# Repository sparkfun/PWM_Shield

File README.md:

**NOTE:** *This product has been retired from our catalog. If you are looking for more up-to-date info, please check out some of these resources to see how other users are still hacking and improving on this product.*
* *[SparkFun Forum](https://forum.sparkfun.com/)*
* *[Comments Here on GitHub](https://github.com/sparkfun/PWM_Shield/issues)*
* *[IRC Channel](https://www.sparkfun.com/news/263)*

SparkFun PWM Shield
========================================

[*SparkFun PWM Shield (DEV-10615)*](https://www.sparkfun.com/products/10615)

This is the Arduino shield version of our TLC5940 Breakout. 
The SparkFun PWM Shield will allow you to generate up to 16 PWM signals from your Arduino by utilizing the power of the TLC5940 IC. 

Repository Contents
-------------------

* **/Hardware** - Eagle design files (.brd, .sch)
* **/Libraries** - Libraries for use with the TLC5940
* **/Production** - Production panel files (.brd)

Documentation
--------------
* **[Library](https://github.com/sparkfun/SparkFun_TLC5940_Arduino_Library)** - Arduino Library for the TLC5940. 
* **[SparkFun Fritzing repo](https://github.com/sparkfun/Fritzing_Parts)** - Fritzing diagrams for SparkFun products.
* **[SparkFun 3D Model repo](https://github.com/sparkfun/3D_Models)** - 3D models of SparkFun products. 

License Information
-------------------
This product is _**open source**_! 

The **hardware** is released under [Creative Commons ShareAlike 4.0 International](https://creativecommons.org/licenses/by-sa/4.0/).

Please use, reuse, and modify these files as you see fit. Please maintain attribution to SparkFun Electronics and release anything derivative under the same license.

Distributed as-is; no warranty is given.

- Your friends at SparkFun.

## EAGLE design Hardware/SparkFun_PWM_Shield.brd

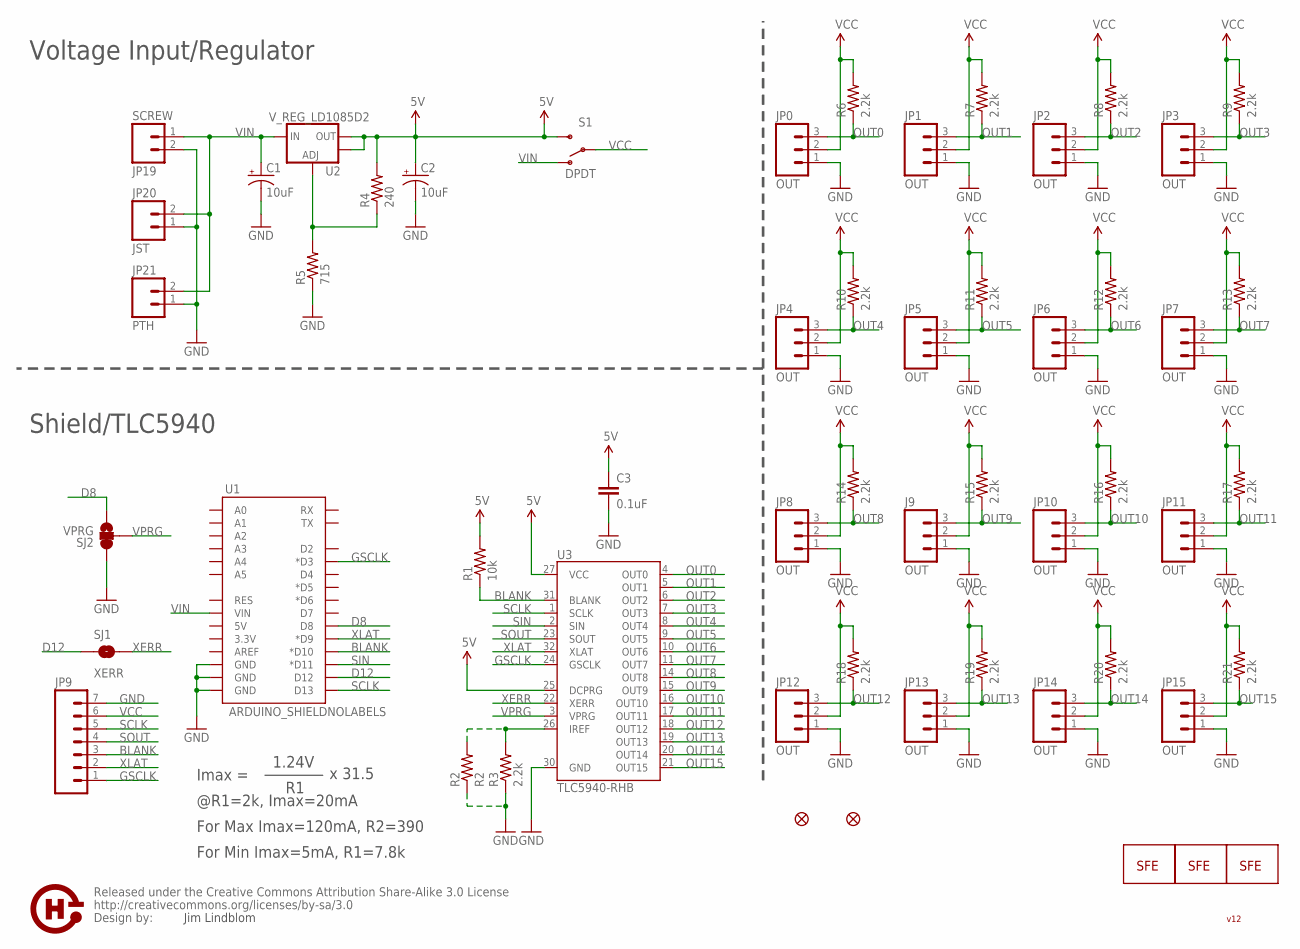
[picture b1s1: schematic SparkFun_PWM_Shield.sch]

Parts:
C1: 10uF; EIA3528
C2: 10uF; EIA3216
C3: 0.1uF; 0402-CAP
J9: OUT; 1X03
JP0, JP1, JP2, JP3, JP4, JP5, JP6, JP7, JP8, JP10, JP11, JP12, JP13, JP14, JP15: OUT; 1X03
JP9: M07; 1X07
JP16: LOGO-SFENEW; SFE-NEW-WEBLOGO
JP17: LOGO-SFESK; SFE-LOGO-FLAME
JP18: LOGO-SFENW2; SFE-NEW-WEB
JP19: SCREW; SCREWTERMINAL-3.5MM-2-NS
JP20: JST; JST-2-PTH
JP21: PTH; 1X02
JP22, JP23: FIDUCIAL1X2; FIDUCIAL-1X2
R1: 10k; 0402-RES
R2: R2; AXIAL-0.3
R3, R6, R7, R8, R9, R10, R11, R12, R13, R14, R15, R16, R17, R18, R19, R20, R21: 2.2k; 0402-RES
R4: 240; 0402-RES
R5: 715; 0402-RES
S1: DPDT; AYZ0202
SJ1: XERR; SJ_2S-NO
SJ2: VPRG; SJ_3
U1: ARDUINO_SHIELDNOLABELS; DUEMILANOVE_SHIELD_NOLABELS
U2: V_REG_LD1085D2; D2PACK/A
U3: TLC5940-RHB; QFN-32
U$1: OSHW-LOGOORB; OSHW-LOGO-GO
U$2: CREATIVE_COMMONS

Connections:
5V: C2.A (+), C3.1, R1.2, R4.2, S1.3 (S), U2.2 (OUT), U2.TAB (OUT), U3.25 (DCPRG), U3.27 (VCC)
BLANK: JP9.3, R1.1, U1.D10 (*D10), U3.31 (BLANK)
D8: SJ2.3, U1.D8
D12: SJ1.1, U1.D12
GND: C1.C (-), C2.C (-), C3.2, J9.1, JP0.1, JP1.1, JP2.1, JP3.1, JP4.1, JP5.1, JP6.1, JP7.1, JP8.1, JP9.7, JP10.1, JP11.1, JP12.1, JP13.1, JP14.1, JP15.1, JP19.2, JP20.1, JP21.1, R2.P$1 (1), R3.1, R5.1, SJ2.1, U1.GND@0 (GND), U1.GND@1 (GND), U1.GND@2 (GND), U3.30 (GND)
GSCLK: JP9.1, U1.D3 (*D3), U3.24 (GSCLK)
unnamed: R4.1, R5.2, U2.1 (ADJ)
unnamed: R2.P$2 (2), R3.2, U3.26 (IREF)
OUT0: JP0.3, R6.1, U3.4 (OUT0)
OUT1: JP1.3, R7.1, U3.5 (OUT1)
OUT2: JP2.3, R8.1, U3.6 (OUT2)
OUT3: JP3.3, R9.1, U3.7 (OUT3)
OUT4: JP4.3, R10.1, U3.8 (OUT4)
OUT5: JP5.3, R11.1, U3.9 (OUT5)
OUT6: JP6.3, R12.1, U3.10 (OUT6)
OUT7: JP7.3, R13.1, U3.11 (OUT7)
OUT8: JP8.3, R14.1, U3.14 (OUT8)
OUT9: J9.3, R15.1, U3.15 (OUT9)
OUT10: JP10.3, R16.1, U3.16 (OUT10)
OUT11: JP11.3, R17.1, U3.17 (OUT11)
OUT12: JP12.3, R18.1, U3.18 (OUT12)
OUT13: JP13.3, R19.1, U3.19 (OUT13)
OUT14: JP14.3, R20.1, U3.20 (OUT14)
OUT15: JP15.3, R21.1, U3.21 (OUT15)
SCLK: JP9.5, U1.D13, U3.1 (SCLK)
SIN: U1.D11 (*D11), U3.2 (SIN)
SOUT: JP9.4, U3.23 (SOUT)
VCC: J9.2, JP0.2, JP1.2, JP2.2, JP3.2, JP4.2, JP5.2, JP6.2, JP7.2, JP8.2, JP9.6, JP10.2, JP11.2, JP12.2, JP13.2, JP14.2, JP15.2, R6.2, R7.2, R8.2, R9.2, R10.2, R11.2, R12.2, R13.2, R14.2, R15.2, R16.2, R17.2, R18.2, R19.2, R20.2, R21.2, S1.2
VIN: C1.A (+), JP19.1, JP20.2, JP21.2, S1.1 (O), U1.VIN, U2.3 (IN)
VPRG: SJ2.2, U3.3 (VPRG)
XERR: SJ1.2, U3.22 (XERR)
XLAT: JP9.2, U1.D9 (*D9), U3.32 (XLAT)

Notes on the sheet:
Imax =
1.24V
x 31.5
@R1=2k, Imax=20mA
For Max Imax=120mA, R2=390
For Min Imax=5mA, R1=7.8k
Jim Lindblom
Shield/TLC5940
Voltage Input/Regulator
v12

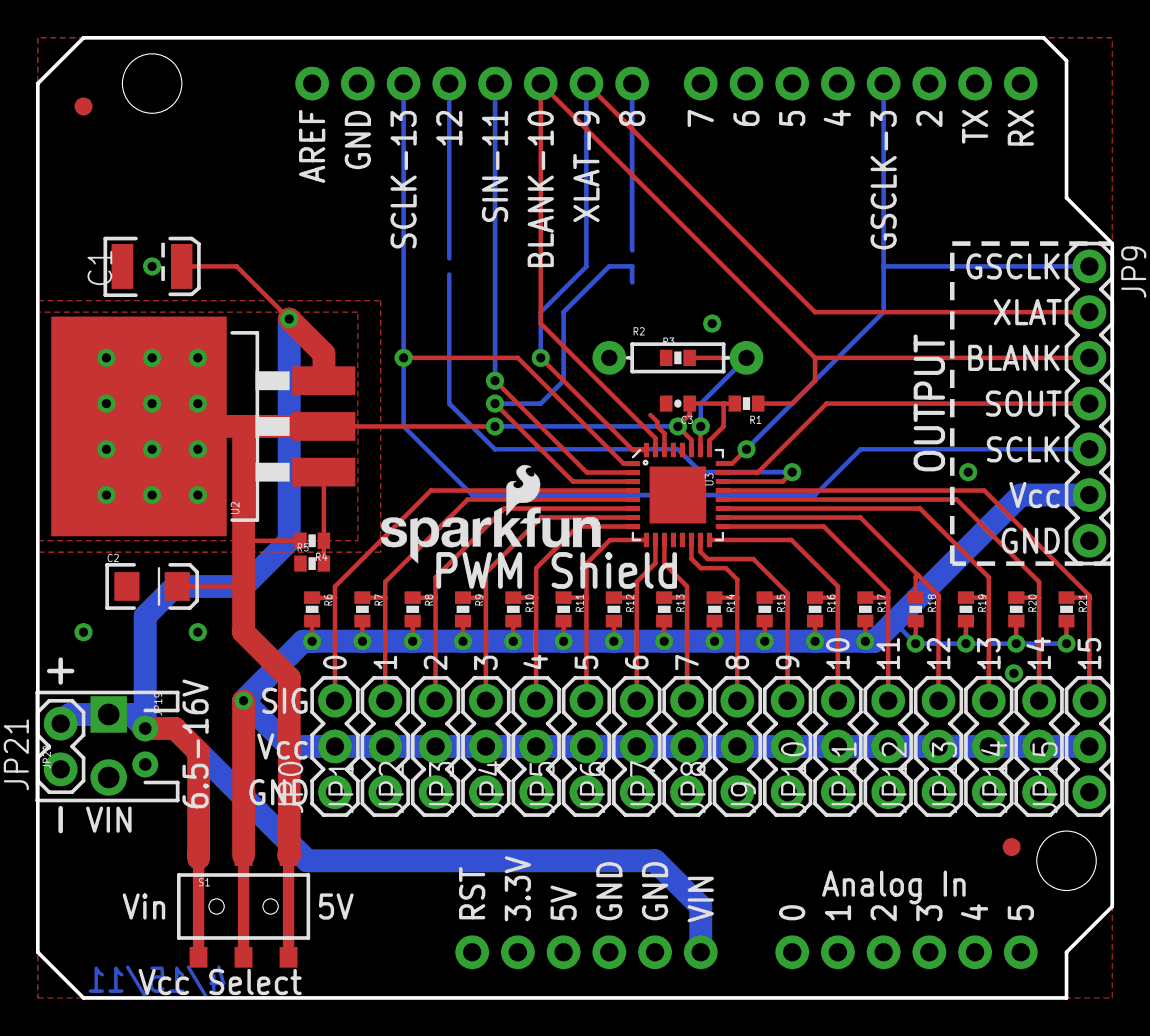
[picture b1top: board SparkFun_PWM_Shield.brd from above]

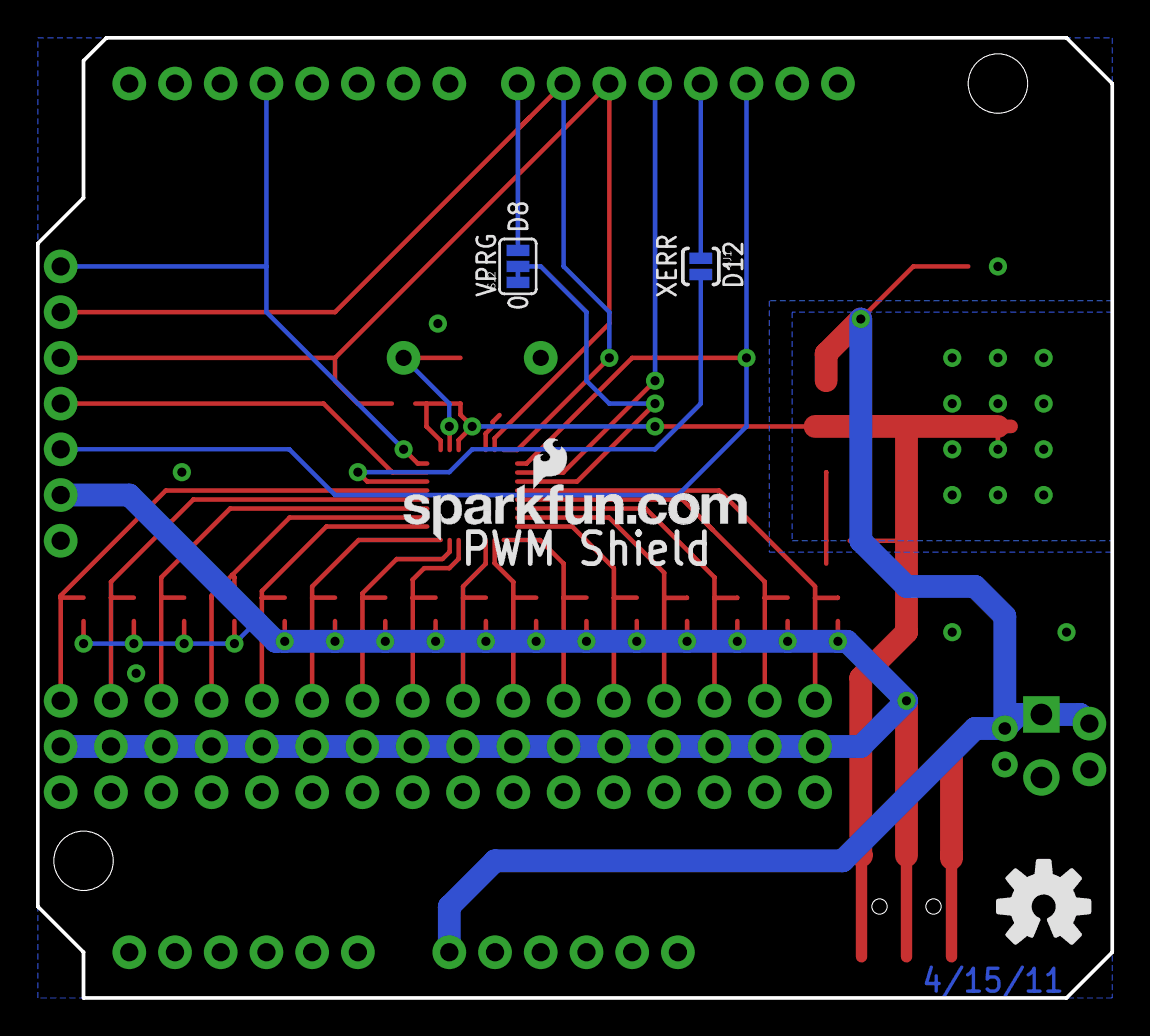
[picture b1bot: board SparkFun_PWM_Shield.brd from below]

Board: 2 copper layers, 59.7 x 53.3 mm, 57 parts (4 on the bottom side), 32 nets.

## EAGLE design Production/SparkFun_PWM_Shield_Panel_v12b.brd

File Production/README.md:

SparkFun Production Files
=========================

These .brd files are the panels we use for producing large numbers of pcbs.

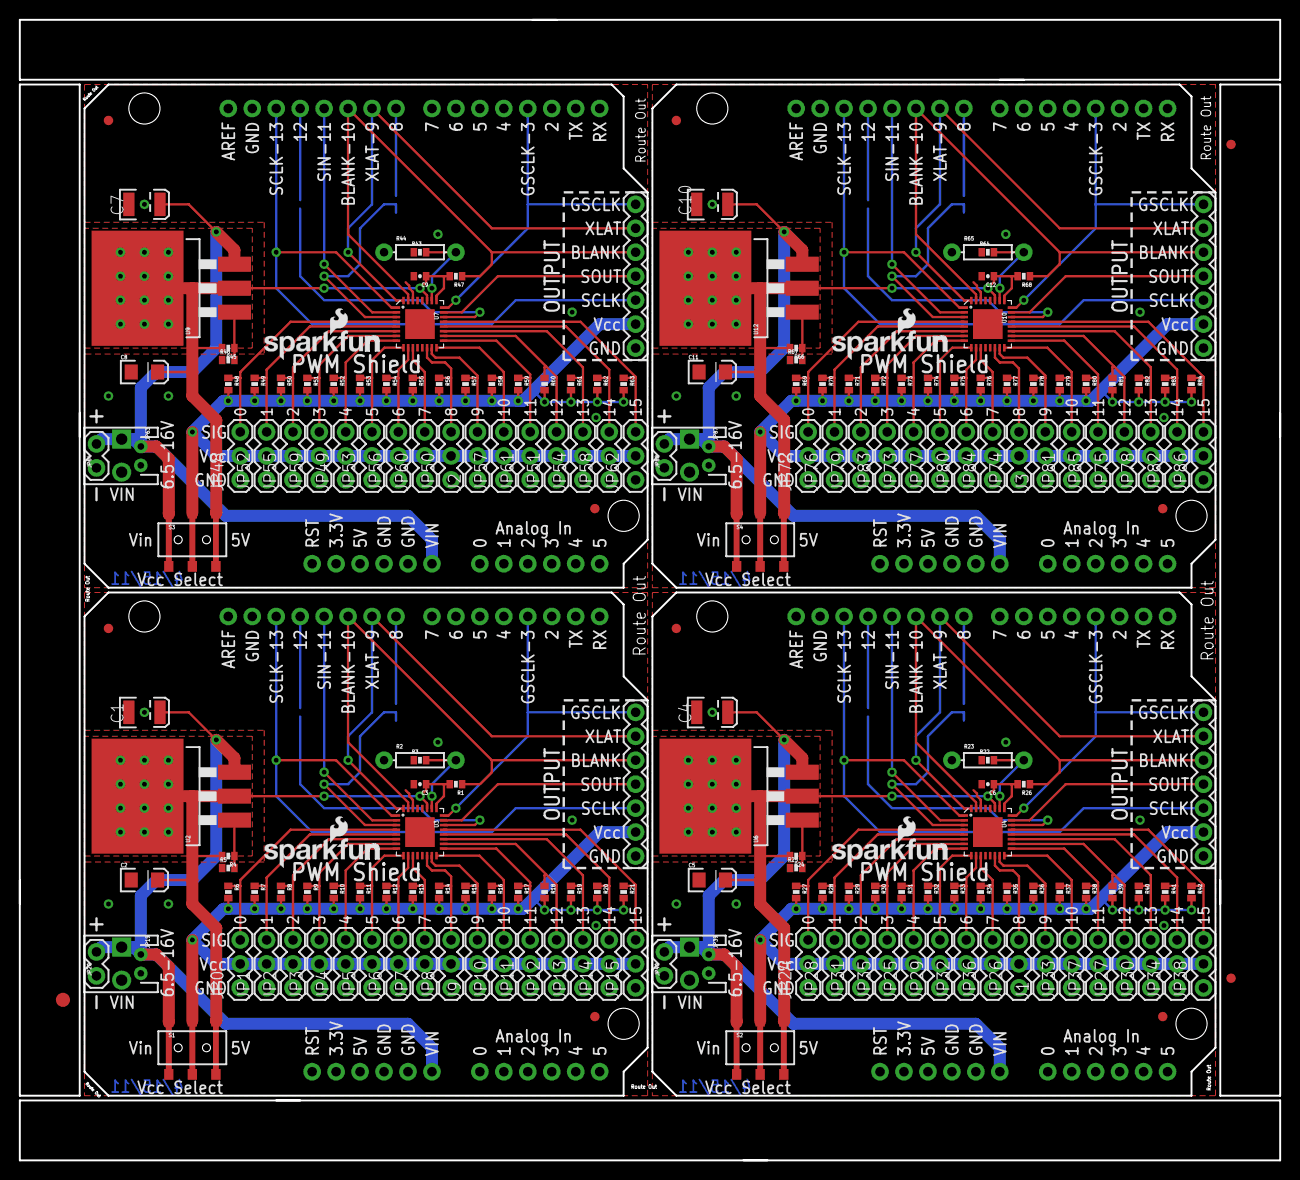
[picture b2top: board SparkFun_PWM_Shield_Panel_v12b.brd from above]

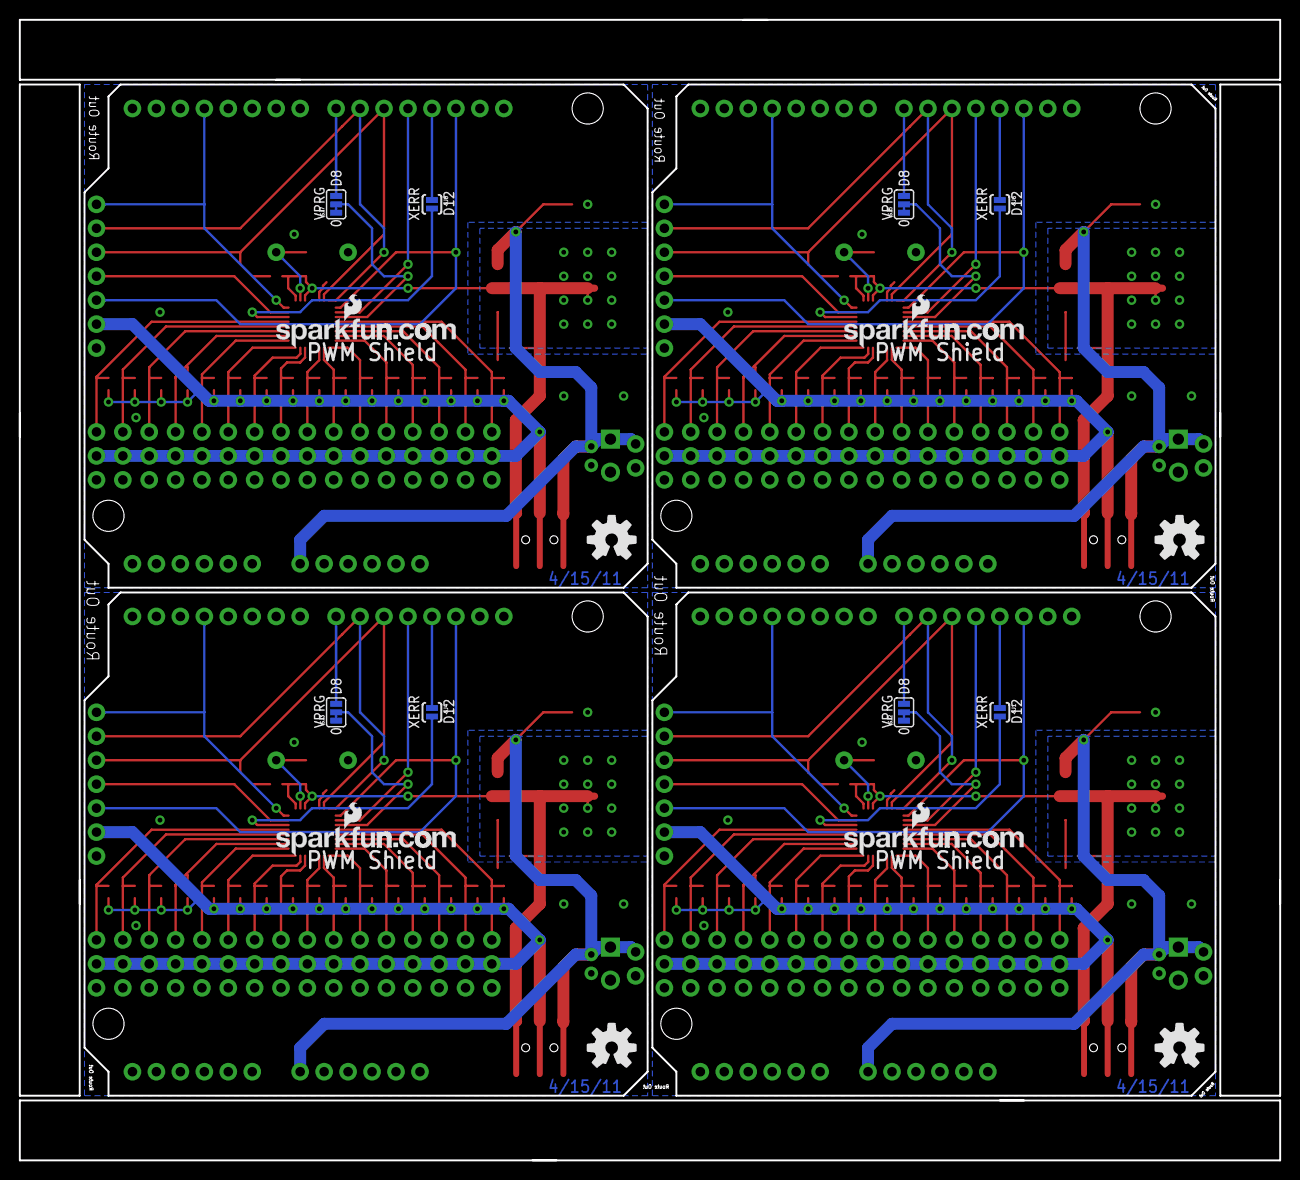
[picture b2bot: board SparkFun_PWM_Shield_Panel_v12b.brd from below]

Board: 2 copper layers, 133.6 x 120.9 mm, 227 parts (16 on the bottom side), 128 nets.

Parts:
C1, C4, C7, C10: 10uF; EIA3528
C2, C5, C8, C11: 10uF; EIA3216
C3, C6, C9, C12: 0.1uF; 0402-CAP
E$1: FIDUCIAL-1.5X3
E$5, E$6: FIDUCIAL-1X2
J1, J2, J3, J9: OUT; 1X03
JP0, JP1, JP2, JP3, JP4, JP5, JP6, JP7, JP8, JP10, JP11, JP12, JP13, JP14, JP15, JP24, JP25, JP26, JP27, JP28, JP29, JP30, JP31, JP32, JP33, JP34, JP35, JP36, JP37, JP38, JP48, JP49, JP50, JP51, JP52, JP53, JP54, JP55, JP56, JP57, JP58, JP59, JP60, JP61, JP62, JP72, JP73, JP74, JP75, JP76, JP77, JP78, JP79, JP80, JP81, JP82, JP83, JP84, JP85, JP86: OUT; 1X03
JP9, JP43, JP67, JP91: 1X07
JP16, JP44, JP68, JP92: LOGO-SFENEW; SFE-NEW-WEBLOGO
JP17, JP45, JP69, JP93: LOGO-SFESK; SFE-LOGO-FLAME
JP18, JP42, JP66, JP90: LOGO-SFENW2; SFE-NEW-WEB
JP19, JP39, JP63, JP87: SCREW; SCREWTERMINAL-3.5MM-2-NS
JP20, JP40, JP64, JP88: JST; JST-2-PTH
JP21, JP41, JP65, JP89: PTH; 1X02
JP22, JP23, JP46, JP47, JP70, JP71, JP94, JP95: FIDUCIAL1X2; FIDUCIAL-1X2
R1, R26, R47, R68: 10k; 0402-RES
R2, R23, R44, R65: R2; AXIAL-0.3
R3, R6, R7, R8, R9, R10, R11, R12, R13, R14, R15, R16, R17, R18, R19, R20, R21, R22, R27, R28, R29, R30, R31, R32, R33, R34, R35, R36, R37, R38, R39, R40, R41, R42, R43, R48, R49, R50, R51, R52, R53, R54, R55, R56, R57, R58, R59, R60, R61, R62, R63, R64, R69, R70, R71, R72, R73, R74, R75, R76, R77, R78, R79, R80, R81, R82, R83, R84: 2.2k; 0402-RES
R4, R24, R45, R66: 240; 0402-RES
R5, R25, R46, R67: 715; 0402-RES
S1, S2, S3, S4: DPDT; AYZ0202
SJ1, SJ4, SJ6, SJ8: XERR; SJ_2S-NO
SJ2, SJ3, SJ5, SJ7: VPRG; SJ_3
U1, U5, U8, U11: ARDUINO_SHIELDNOLABELS; DUEMILANOVE_SHIELD_NOLABELS
U2, U6, U9, U12: V_REG_LD1085D2; D2PACK/A
U3, U4, U7, U10: TLC5940-RHB; QFN-32
U$1, U$2, U$3, U$4: OSHW-LOGOORB; OSHW-LOGO-GO

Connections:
5V: C2.A, C3.1, R1.2, R4.2, S1.3, U2.2, U2.TAB, U3.25, U3.27
5V1: C5.A, C6.1, R24.2, R26.2, S2.3, U4.25, U4.27, U6.2, U6.TAB
5V2: C8.A, C9.1, R45.2, R47.2, S3.3, U7.25, U7.27, U9.2, U9.TAB
5V3: C11.A, C12.1, R66.2, R68.2, S4.3, U10.25, U10.27, U12.2, U12.TAB
BLANK: JP9.3, R1.1, U1.D10, U3.31
BLANK1: JP43.3, R26.1, U4.31, U5.D10
BLANK2: JP67.3, R47.1, U7.31, U8.D10
BLANK3: JP91.3, R68.1, U10.31, U11.D10
D1: SJ3.3, U5.D8
D2: SJ4.1, U5.D12
D3: SJ5.3, U8.D8
D4: SJ6.1, U8.D12
D5: SJ7.3, U11.D8
D6: SJ8.1, U11.D12
D8: SJ2.3, U1.D8
D12: SJ1.1, U1.D12
GND: C1.C, C2.C, C3.2, J9.1, JP0.1, JP1.1, JP2.1, JP3.1, JP4.1, JP5.1, JP6.1, JP7.1, JP8.1, JP9.7, JP10.1, JP11.1, JP12.1, JP13.1, JP14.1, JP15.1, JP19.2, JP20.1, JP21.1, R2.P$1, R3.1, R5.1, SJ2.1, U1.GND@0, U1.GND@1, U1.GND@2, U3.30
GND1: C4.C, C5.C, C6.2, J1.1, JP24.1, JP25.1, JP26.1, JP27.1, JP28.1, JP29.1, JP30.1, JP31.1, JP32.1, JP33.1, JP34.1, JP35.1, JP36.1, JP37.1, JP38.1, JP39.2, JP40.1, JP41.1, JP43.7, R22.1, R23.P$1, R25.1, SJ3.1, U4.30, U5.GND@0, U5.GND@1, U5.GND@2
GND2: C7.C, C8.C, C9.2, J2.1, JP48.1, JP49.1, JP50.1, JP51.1, JP52.1, JP53.1, JP54.1, JP55.1, JP56.1, JP57.1, JP58.1, JP59.1, JP60.1, JP61.1, JP62.1, JP63.2, JP64.1, JP65.1, JP67.7, R43.1, R44.P$1, R46.1, SJ5.1, U7.30, U8.GND@0, U8.GND@1, U8.GND@2
GND3: C10.C, C11.C, C12.2, J3.1, JP72.1, JP73.1, JP74.1, JP75.1, JP76.1, JP77.1, JP78.1, JP79.1, JP80.1, JP81.1, JP82.1, JP83.1, JP84.1, JP85.1, JP86.1, JP87.2, JP88.1, JP89.1, JP91.7, R64.1, R65.P$1, R67.1, SJ7.1, U10.30, U11.GND@0, U11.GND@1, U11.GND@2
GSCLK: JP9.1, U1.D3, U3.24
GSCLK1: JP43.1, U4.24, U5.D3
GSCLK2: JP67.1, U7.24, U8.D3
GSCLK3: JP91.1, U10.24, U11.D3
unnamed: R22.2, R23.P$2, U4.26
unnamed: R4.1, R5.2, U2.1
unnamed: R24.1, R25.2, U6.1
unnamed: R43.2, R44.P$2, U7.26
unnamed: R45.1, R46.2, U9.1
unnamed: R64.2, R65.P$2, U10.26
unnamed: R66.1, R67.2, U12.1
unnamed: R2.P$2, R3.2, U3.26
OUT0: JP0.3, R6.1, U3.4
OUT1: JP1.3, R7.1, U3.5
OUT2: JP2.3, R8.1, U3.6
OUT3: JP3.3, R9.1, U3.7
OUT4: JP4.3, R10.1, U3.8
OUT5: JP5.3, R11.1, U3.9
OUT6: JP6.3, R12.1, U3.10
OUT7: JP7.3, R13.1, U3.11
OUT8: JP8.3, R14.1, U3.14
OUT9: J9.3, R15.1, U3.15
OUT10: JP10.3, R16.1, U3.16
OUT11: JP11.3, R17.1, U3.17
OUT12: JP12.3, R18.1, U3.18
OUT13: JP13.3, R19.1, U3.19
OUT14: JP14.3, R20.1, U3.20
OUT15: JP15.3, R21.1, U3.21
OUT16: JP24.3, R27.1, U4.4
OUT17: JP31.3, R29.1, U4.6
OUT18: JP28.3, R28.1, U4.5
OUT19: JP35.3, R30.1, U4.7
OUT20: JP25.3, R31.1, U4.8
OUT21: JP29.3, R32.1, U4.9
OUT22: JP32.3, R33.1, U4.10
OUT23: JP36.3, R34.1, U4.11
OUT24: JP26.3, R35.1, U4.14
OUT25: J1.3, R36.1, U4.15
OUT26: JP33.3, R37.1, U4.16
OUT27: JP37.3, R38.1, U4.17
OUT28: JP27.3, R39.1, U4.18
OUT29: JP30.3, R40.1, U4.19
OUT30: JP34.3, R41.1, U4.20
OUT31: JP38.3, R42.1, U4.21
OUT32: JP48.3, R48.1, U7.4
OUT33: JP55.3, R50.1, U7.6
OUT34: JP52.3, R49.1, U7.5
OUT35: JP59.3, R51.1, U7.7
OUT36: JP49.3, R52.1, U7.8
OUT37: JP53.3, R53.1, U7.9
OUT38: JP56.3, R54.1, U7.10
OUT39: JP60.3, R55.1, U7.11
OUT40: JP50.3, R56.1, U7.14
OUT41: J2.3, R57.1, U7.15
OUT42: JP57.3, R58.1, U7.16
OUT43: JP61.3, R59.1, U7.17
OUT44: JP51.3, R60.1, U7.18
OUT45: JP54.3, R61.1, U7.19
OUT46: JP58.3, R62.1, U7.20
OUT47: JP62.3, R63.1, U7.21
OUT48: JP72.3, R69.1, U10.4
OUT49: JP79.3, R71.1, U10.6
OUT50: JP76.3, R70.1, U10.5
OUT51: JP83.3, R72.1, U10.7
OUT52: JP73.3, R73.1, U10.8
OUT53: JP77.3, R74.1, U10.9
OUT54: JP80.3, R75.1, U10.10
OUT55: JP84.3, R76.1, U10.11
OUT56: JP74.3, R77.1, U10.14
OUT57: J3.3, R78.1, U10.15
OUT58: JP81.3, R79.1, U10.16
OUT59: JP85.3, R80.1, U10.17
OUT60: JP75.3, R81.1, U10.18
OUT61: JP78.3, R82.1, U10.19
OUT62: JP82.3, R83.1, U10.20
OUT63: JP86.3, R84.1, U10.21
SCLK: JP9.5, U1.D13, U3.1
SCLK1: JP43.5, U4.1, U5.D13
SCLK2: JP67.5, U7.1, U8.D13
SCLK3: JP91.5, U10.1, U11.D13
SIN: U1.D11, U3.2
SIN1: U4.2, U5.D11
SIN2: U7.2, U8.D11
SIN3: U10.2, U11.D11
SOUT: JP9.4, U3.23
SOUT1: JP43.4, U4.23
SOUT2: JP67.4, U7.23
SOUT3: JP91.4, U10.23
VCC: J9.2, JP0.2, JP1.2, JP2.2, JP3.2, JP4.2, JP5.2, JP6.2, JP7.2, JP8.2, JP9.6, JP10.2, JP11.2, JP12.2, JP13.2, JP14.2, JP15.2, R6.2, R7.2, R8.2, R9.2, R10.2, R11.2, R12.2, R13.2, R14.2, R15.2, R16.2, R17.2, R18.2, R19.2, R20.2, R21.2, S1.2
VCC1: J1.2, JP24.2, JP25.2, JP26.2, JP27.2, JP28.2, JP29.2, JP30.2, JP31.2, JP32.2, JP33.2, JP34.2, JP35.2, JP36.2, JP37.2, JP38.2, JP43.6, R27.2, R28.2, R29.2, R30.2, R31.2, R32.2, R33.2, R34.2, R35.2, R36.2, R37.2, R38.2, R39.2, R40.2, R41.2, R42.2, S2.2
VCC2: J2.2, JP48.2, JP49.2, JP50.2, JP51.2, JP52.2, JP53.2, JP54.2, JP55.2, JP56.2, JP57.2, JP58.2, JP59.2, JP60.2, JP61.2, JP62.2, JP67.6, R48.2, R49.2, R50.2, R51.2, R52.2, R53.2, R54.2, R55.2, R56.2, R57.2, R58.2, R59.2, R60.2, R61.2, R62.2, R63.2, S3.2
VCC3: J3.2, JP72.2, JP73.2, JP74.2, JP75.2, JP76.2, JP77.2, JP78.2, JP79.2, JP80.2, JP81.2, JP82.2, JP83.2, JP84.2, JP85.2, JP86.2, JP91.6, R69.2, R70.2, R71.2, R72.2, R73.2, R74.2, R75.2, R76.2, R77.2, R78.2, R79.2, R80.2, R81.2, R82.2, R83.2, R84.2, S4.2
VIN: C1.A, JP19.1, JP20.2, JP21.2, S1.1, U1.VIN, U2.3
VIN1: C4.A, JP39.1, JP40.2, JP41.2, S2.1, U5.VIN, U6.3
VIN2: C7.A, JP63.1, JP64.2, JP65.2, S3.1, U8.VIN, U9.3
VIN3: C10.A, JP87.1, JP88.2, JP89.2, S4.1, U11.VIN, U12.3
VPRG: SJ2.2, U3.3
VPRG1: SJ3.2, U4.3
VPRG2: SJ5.2, U7.3
VPRG3: SJ7.2, U10.3
XERR: SJ1.2, U3.22
XERR1: SJ4.2, U4.22
XERR2: SJ6.2, U7.22
XERR3: SJ8.2, U10.22
XLAT: JP9.2, U1.D9, U3.32
XLAT1: JP43.2, U4.32, U5.D9
XLAT2: JP67.2, U7.32, U8.D9
XLAT3: JP91.2, U10.32, U11.D9

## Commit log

2015-04-29 Initial board file commit
2015-04-29 Squashed 'Libraries/Arduino/' content from commit 09ea0f2
    git-subtree-dir: Libraries/Arduino
    git-subtree-split: 09ea0f29b5f23ba79426c3c33b837437829adf9c
2015-04-29 Adding library update instructions
2015-06-08 Squashed 'Libraries/Arduino/' changes from 09ea0f2..7814504
    7814504 Fixing library.properties file
    git-subtree-dir: Libraries/Arduino
    git-subtree-split: 78145041dbf402e7b9f9ce5dbe52a36ebba0e697
2015-10-05 Squashed 'Libraries/Arduino/' changes from 7814504..7c3d8c7
    7c3d8c7 Fixing compilation error
    84f472c Fixing library.properties to enable loading in Arduino IDE
    git-subtree-dir: Libraries/Arduino
    git-subtree-split: 7c3d8c7861b762511ad4b3e899ffde8689cd396d
2015-12-23 created panel v12b
2016-01-11 Squashed 'Libraries/Arduino/' changes from 7c3d8c7..18a0c0f
    18a0c0f Updating file names for codebender fix
    git-subtree-dir: Libraries/Arduino
    git-subtree-split: 18a0c0fa8911f19f615ccea7981273a6ffd0adf4

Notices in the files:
parts and their libraries:
SparkFun: Released under the Creative Commons Attribution Share-Alike 3.0 License
SparkFun: http://creativecommons.org/licenses/by-sa/3.0
SparkFun-Aesthetics: Licensing: CC v3.0 Share-Alike You are welcome to use this library for commercial purposes.
